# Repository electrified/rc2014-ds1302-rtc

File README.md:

# DS1302 Real Time Clock for the RC2014 computer

## The board
RomWBW has code to support a DS1302 Real Time Clock, enabling files to be timestamped and other timekeeping operations. This board implements the clock in a standard way for the RC2014. 

The design is largely based on the clock implementation on the [RetroBrew Computers SBC V2](https://retrobrewcomputers.org/doku.php?id=boards:sbc:sbc_v2:start) and [Zeta SBC V2](http://www.malinov.com/Home/sergeys-projects/zeta-sbc-v2).

## What can you use this for?
Telling the time :)

## Getting started with RomWBW

Set ```DSRTCENABLE``` to true in the configuration and rebuild your ROM image.

On startup you will see the time shown.

ZSystem has more complete support for time utilities than CP/M. After booting into ZSystem by pressing Z, Run ```ldds``` to load the resident time driver. ```td``` can then be used to set the time as well as view it.

In CP/M ```RTC.com``` can be used for querying and setting the clock but it is very basic.

## Jumpers
SW1 - Address configuration. For the default address of 0xC0, set switches 5 and 6 to on.

## Bill Of Materials

Reference| Value|Farnell part no|Rapid part no|Digi-key part no|
---------|------|---------------|-------------|----------------|
P1|1x39 right angled pin header|||732-5350-ND|
BT1|Keystone 106 20mm battery holder for CR2032|1650672||36-106-ND|
BT1|CR2032 battery|||P189-ND|
U1|CD74HCT688E COMPARATOR, SINGLE, PDIP-20|2407104||296-2131-5-ND|
U2|SN74HCT125N LOGIC, BUS BUFF TRI-ST QD, 14DIP|1739676||296-8386-5-ND|
U3|CD74HCT174E 74HCT CMOS, 74HCT174, DIP16, 5.5V|1105983||296-2100-5-ND|
U4|DS1302N+ RTC W/ RAM, 248B, D-D-M-Y, HH:MM:SS, DIP|2515367||DS1302N+-ND|
U5|SN74HCT32N IC, QUAD 2-INPUT OR, 74HCT32, DIP14|9591982||296-1615-5-ND|
C1-5|0.1uF MLCC capacitor|||BC2665CT-ND|
Y1|32.768 kHz crystal|9712887||535-9034-ND|
RN1|10k 8 Pin Commoned Resistor Network||63-0125|4608X-1-103LF-ND|
SW1|6 way DIL switch||80-0338|CT2066-ND|
U1|CONN IC DIP SOCKET 20POS TIN|||AE10015-ND|
U2|CONN IC DIP SOCKET 14POS TIN|||AE10012-ND|
U3|CONN IC DIP SOCKET 16POS TIN|||AE10013-ND|
U4|CONN IC DIP SOCKET 8POS TIN|||AE10011-ND|
U5|CONN IC DIP SOCKET 14POS TIN|||AE10012-ND|

## Construction tips
The footprint for the battery holder is designed for a Keystone 106, other battery holders should work if the pins are ~20.5mm apart, which seems to be fairly standard.

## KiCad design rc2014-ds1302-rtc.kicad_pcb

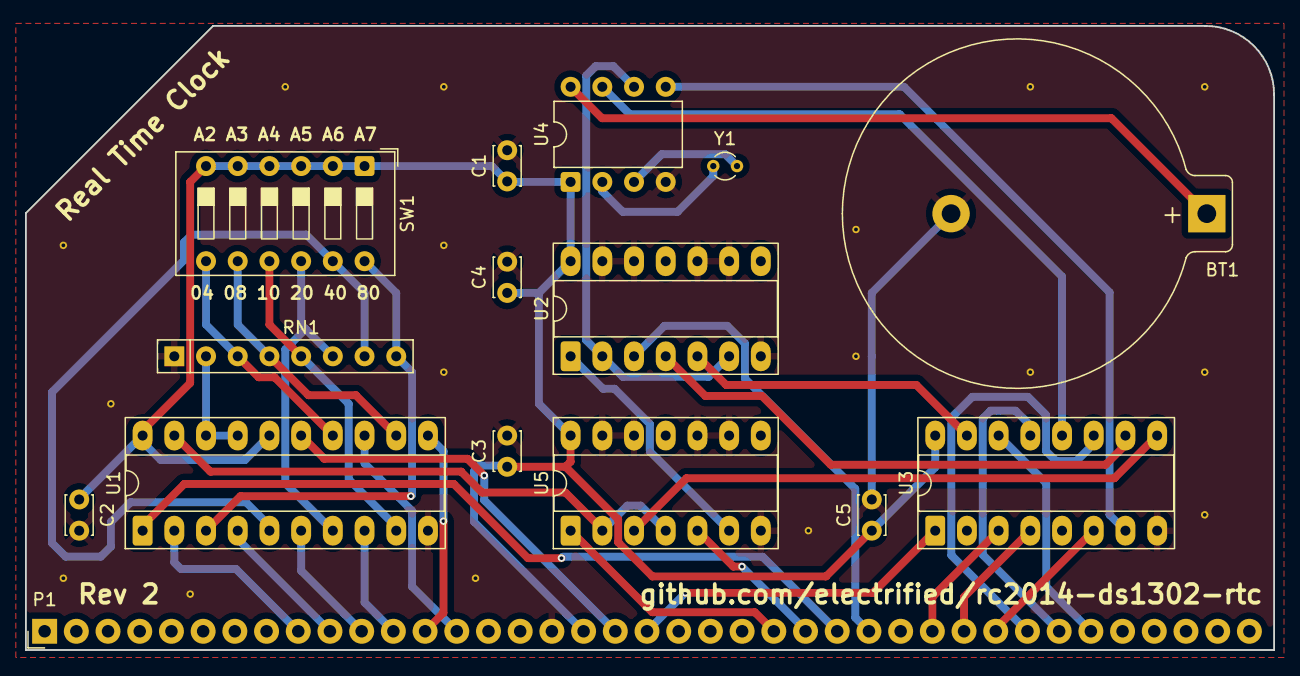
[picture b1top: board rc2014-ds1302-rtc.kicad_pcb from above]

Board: 2 copper layers, 100.0 x 50.0 mm, 15 parts (0 on the bottom side), 38 nets.

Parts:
BT1: Battery_Cell; BatteryHolder_Keystone_106_1x20mm
C1, C2, C3, C4, C5: 0.1uF; C_Disc_D3.0mm_W2.0mm_P2.50mm
P1: RC2014 BUS; Pin_Header_Straight_1x39_Pitch2.54mm_NoSilk
RN1: 10K; R_Array_SIP8
SW1: SW_DIP_x06; SW_DIP_SPSTx06_Slide_9.78x17.42mm_W7.62mm_P2.54mm
U1: 74HCT688; DIP-20_W7.62mm_Socket_LongPads
U2: 74HCT125; DIP-14_W7.62mm_Socket_LongPads
U3: 74HCT174; DIP-16_W7.62mm_Socket_LongPads
U4: DS1302+; DIP-8_W7.62mm
U5: 74HCT32; DIP-14_W7.62mm_Socket_LongPads
Y1: Crystal; Crystal_Round_D2.0mm_Vertical

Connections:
/A2: P1.14, U1.13 (P5)
/A3: P1.13, U1.11 (P4)
/A4: P1.12, U1.8 (P3)
/A5: P1.11, U1.6 (P2)
/A6: P1.10, U1.4 (P1)
/A7: P1.9, U1.2 (P0)
/D0: P1.27, U2.3
/D2: P1.29, U3.3 (D0)
/D3: P1.30, U3.4 (D1)
/D4: P1.31, U3.6 (D2)
/D5: P1.32, U3.11 (D3)
/D6: P1.33, U3.13 (D4)
/D7: P1.34, U3.14 (D5)
/RTC_CE: U3.7 (Q2), U4.5 (CE)
/RTC_CLK: U3.12 (Q4), U4.7 (SCLK)
/RTC_IN: U2.5, U3.15 (Q5)
/RTC_IO: U2.2, U2.6, U4.6 (I/O)
/RTC_WE: U2.4, U3.10 (Q3)
//CS_RTC: U1.19 (P=R), U5.2, U5.4
//IORQ: P1.26, U1.1 (G)
//M1: P1.19, U1.15 (P6)
//RD: P1.25, U5.5
//RESET: P1.20, U3.1 (~Mr)
//RTC_RD: U2.1, U5.6
//RTC_WR: U3.9 (Cp), U5.3
//WR: P1.24, U5.1
GND: BT1.2 (-), C1.2, C2.2, C3.2, C4.2, C5.2, P1.17, RN1.1 (common), U1.10 (GND), U2.7 (GND), U2.9, U2.10, U2.12, U2.13, U3.8 (GND), U4.4 (GND), U5.7 (GND), U5.9, U5.10, U5.12, U5.13
unnamed: BT1.1 (+), U4.8 (VCC1)
unnamed: RN1.2 (R1), U1.17 (P7), U1.18 (R7)
unnamed: RN1.3 (R2), SW1.7, U1.14 (R5)
unnamed: RN1.4 (R3), SW1.8, U1.12 (R4)
unnamed: RN1.5 (R4), SW1.9, U1.9 (R3)
unnamed: RN1.6 (R5), SW1.10, U1.7 (R2)
unnamed: RN1.7 (R6), SW1.11, U1.5 (R1)
unnamed: RN1.8 (R7), SW1.12, U1.3 (R0)
unnamed: U4.2 (X1), Y1.1
unnamed: U4.3 (X2), Y1.2
VCC: C1.1, C2.1, C3.1, C4.1, C5.1, P1.18, SW1.1, SW1.2, SW1.3, SW1.4, SW1.5, SW1.6, U1.16 (R6), U1.20 (VCC), U2.14 (VCC), U3.16 (VCC), U4.1 (VCC2), U5.14 (VCC)

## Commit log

2018-01-03 start pcb layout
2018-01-04 after autoroute
2018-01-21 Think this is ready for manufacturing...
2018-01-30 Add schematic pdf and renders of pcb
2018-02-05 Add digikey part numbers
2020-04-30 Add attribution to retrobrew computers/ Zeta SBC
2020-04-30 fix typo
2022-03-09 Start kicad 6 migration
2022-10-18 Complete kicad 6 migration
2024-06-28 Start kicad 8 migration
2025-07-06 some updates for kicad 9 - still quite a lot of DRC failures
